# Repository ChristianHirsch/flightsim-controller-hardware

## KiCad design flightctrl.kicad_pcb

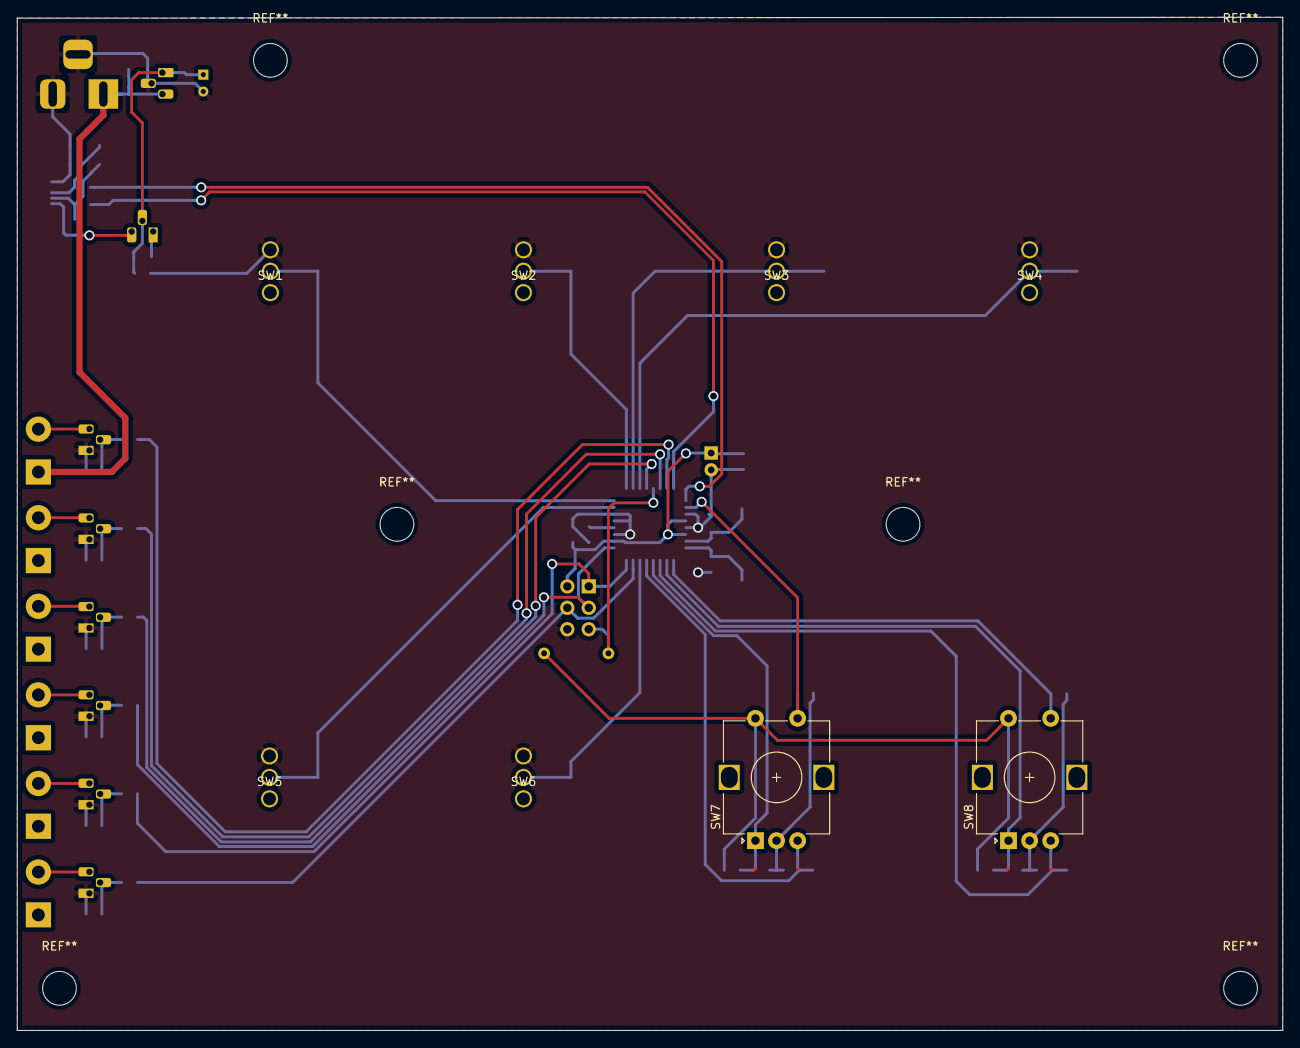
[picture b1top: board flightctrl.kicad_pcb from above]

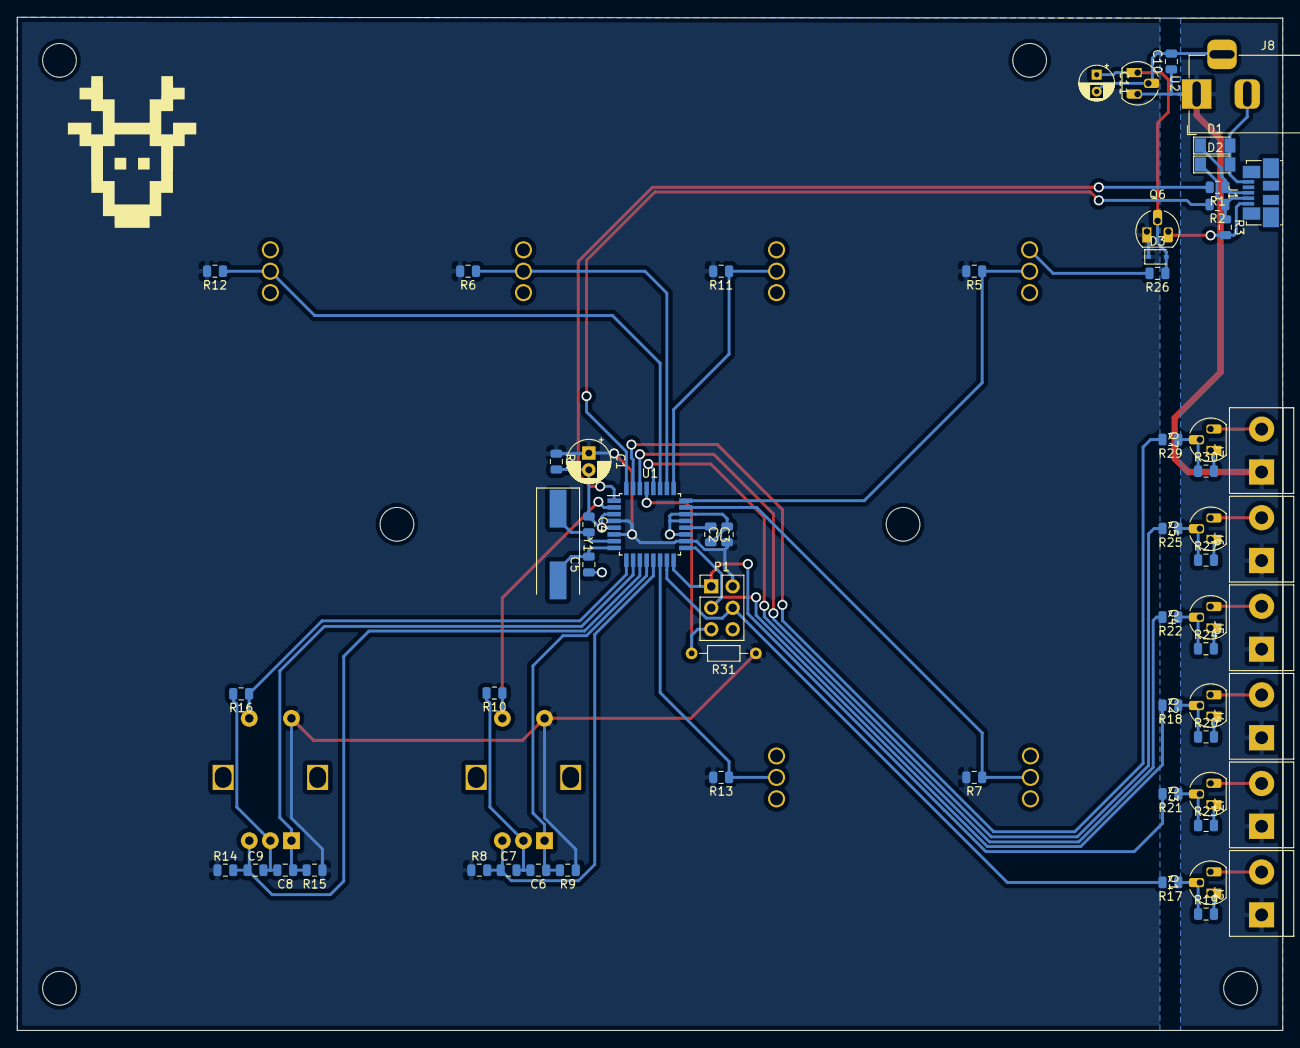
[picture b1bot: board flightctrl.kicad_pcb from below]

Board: 2 copper layers, 150.0 x 120.1 mm, 71 parts (63 on the bottom side), 43 nets.

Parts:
C1: 10µ; CP_Radial_D5.0mm_P2.00mm
C2, C3, C6, C7, C8, C9: 100n; C_0805_2012Metric
C4, C5: 27p; C_0805_2012Metric
C10: 0.1u; C_0805_2012Metric
C11: 100u; CP_Radial_D4.0mm_P2.00mm
D1, D2: D_Zener; D_MiniMELF
D3: BAT20J; D_SOD-323
J1: USB_OTG; USB_Micro-B_Molex_47346-0001
J2, J3, J4, J5, J6, J7: CONN_01X02; TerminalBlock_bornier-2_P5.08mm
J8: BARREL_JACK; BarrelJack_Horizontal
P1: CONN_02X03; PinHeader_2x03_P2.54mm_Vertical
Q1, Q2, Q3, Q4, Q5, Q7: 2N7000; TO-92_HandSolder
Q6: Q_PMOS_SGD; TO-92_HandSolder
R1, R2, R17, R18, R21, R22, R25, R29: 68; R_0805_2012Metric
R3: 1.5k; R_0805_2012Metric
R4: 56k; R_0805_2012Metric
R5, R6, R7, R8, R9, R10, R11, R12, R13, R14, R15, R16, R19, R20, R23, R24, R26, R27, R30: 10k; R_0805_2012Metric
R31: 10k; R_Axial_DIN0204_L3.6mm_D1.6mm_P7.62mm_Horizontal
SW1, SW2, SW3, SW4, SW5, SW6: SW_SPST; MKIP1PUM
SW7, SW8: Rotary_Encoder_Switch; RotaryEncoder_Alps_EC12E-Switch_Vertical_H20mm
U1: ATMEGA328P-AU; TQFP-32_7x7mm_P0.8mm
U2: LM2931AZ-5.0; TO-92_HandSolder
Y1: 12MHz; Crystal_SMD_HC49-SD

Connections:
+5V: C1.1, C2.1, D3.1, P1.2, Q6.1, R4.1, R5.2, R6.2, R7.2, R8.1, R9.1, R11.2, R12.2, R13.2, R14.1, R15.1, R31.1, SW7.S1, SW8.S1, U1.4, U1.6, U1.18
+12V: C10.1, J2.1, J3.1, J4.1, J5.1, J6.1, J7.1, J8.1, U2.3
/Output/O1: J2.2, Q1.3
/Output/O2: J3.2, Q3.3
/Output/O3: J4.2, Q2.3
/Output/O4: J5.2, Q4.3
/Output/O5: J6.2, Q5.3
/Output/O6: J7.2, Q7.3
GND: C1.2, C2.2, C3.2, C4.1, C5.1, C6.2, C7.2, C8.2, C9.2, C10.2, C11.2, D1.2, D2.2, J1.5, J8.2, J8.3, P1.6, Q1.1, Q2.1, Q3.1, Q4.1, Q5.1, Q7.1, R4.2, R10.2, R16.2, R19.2, R20.2, R23.2, R24.2, R26.2, R27.2, R30.2, SW1.2, SW2.2, SW3.2, SW4.2, SW5.2, SW6.2, SW7.C, SW8.C, U1.3, U1.5, U1.19, U1.21, U1.22, U2.2
unnamed: C3.1, U1.20
unnamed: C4.2, U1.7, Y1.1
unnamed: C5.2, U1.8, Y1.2
unnamed: C11.1, D3.2, Q6.2, R26.1, U2.1
unnamed: D1.1, J1.3, R1.1
unnamed: D2.1, J1.2, R2.1, R3.1
unnamed: J1.1, Q6.3, R3.2
unnamed: P1.5, R31.2, U1.29
unnamed: Q1.2, R17.1, R19.1
unnamed: Q2.2, R18.1, R20.1
unnamed: Q3.2, R21.1, R23.1
unnamed: Q4.2, R22.1, R24.1
unnamed: Q5.2, R25.1, R27.1
unnamed: Q7.2, R29.1, R30.1
OUT1: P1.4, R17.2, U1.15
OUT2: P1.1, R21.2, U1.16
OUT3: P1.3, R18.2, U1.17
OUT4: R22.2, U1.28
OUT5: R25.2, U1.30
OUT6: R29.2, U1.31
SW1: R5.1, SW1.1, U1.24
SW2: R11.1, SW2.1, U1.25
SW3: R6.1, SW3.1, U1.26
SW4: R12.1, SW4.1, U1.27
SW5: R7.1, SW5.1, U1.23
SW6: R13.1, SW6.1, U1.14
SW7_A: C6.1, R9.2, SW7.A, U1.12
SW7_B: C7.1, R8.2, SW7.B, U1.13
SW7_C: R10.1, SW7.S2, U1.2
SW8_A: C8.1, R15.2, SW8.A, U1.10
SW8_B: C9.1, R14.2, SW8.B, U1.11
SW8_C: R16.1, SW8.S2, U1.9
USB_DM: R2.2, U1.32
USB_DP: R1.2, U1.1

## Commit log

2017-12-10 initial commit
    (moved from other repo)
2017-12-11 update schematics
2018-03-11 create new hardware schematic and layout
2018-04-02 minors
2018-08-02 update project for KiCAD 5.0, recreate/fix PCB
